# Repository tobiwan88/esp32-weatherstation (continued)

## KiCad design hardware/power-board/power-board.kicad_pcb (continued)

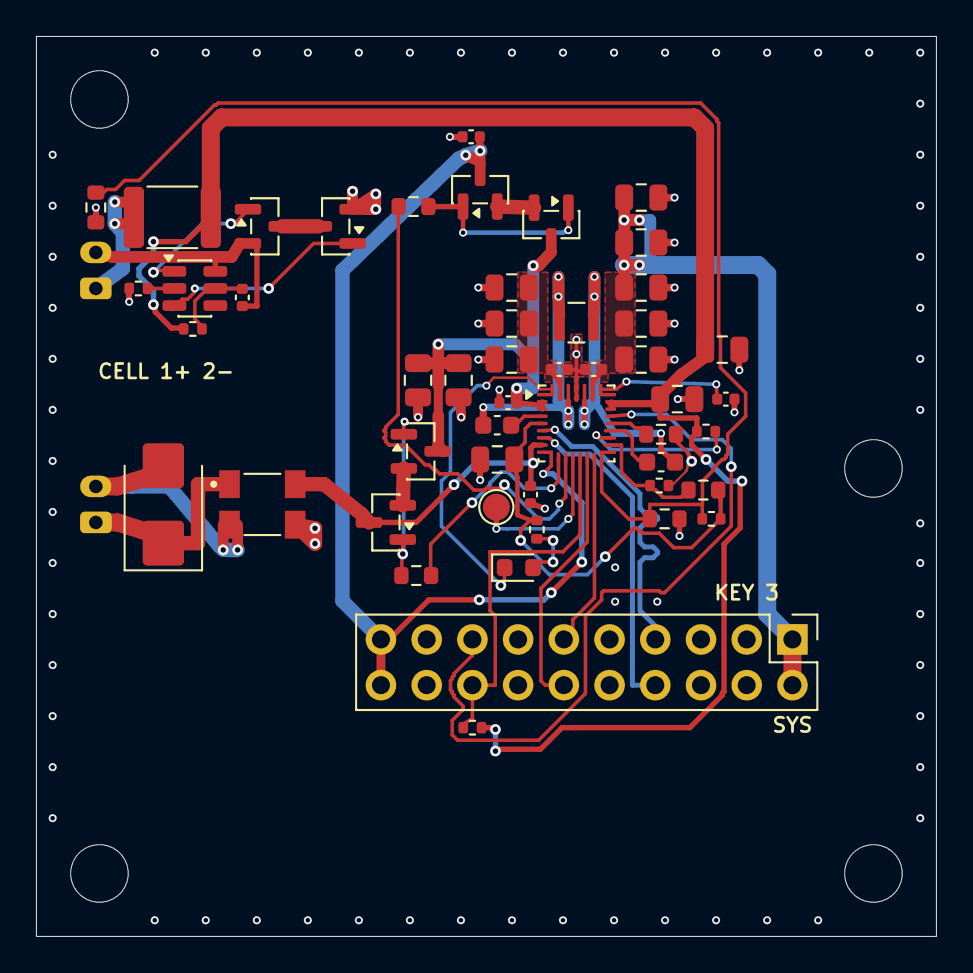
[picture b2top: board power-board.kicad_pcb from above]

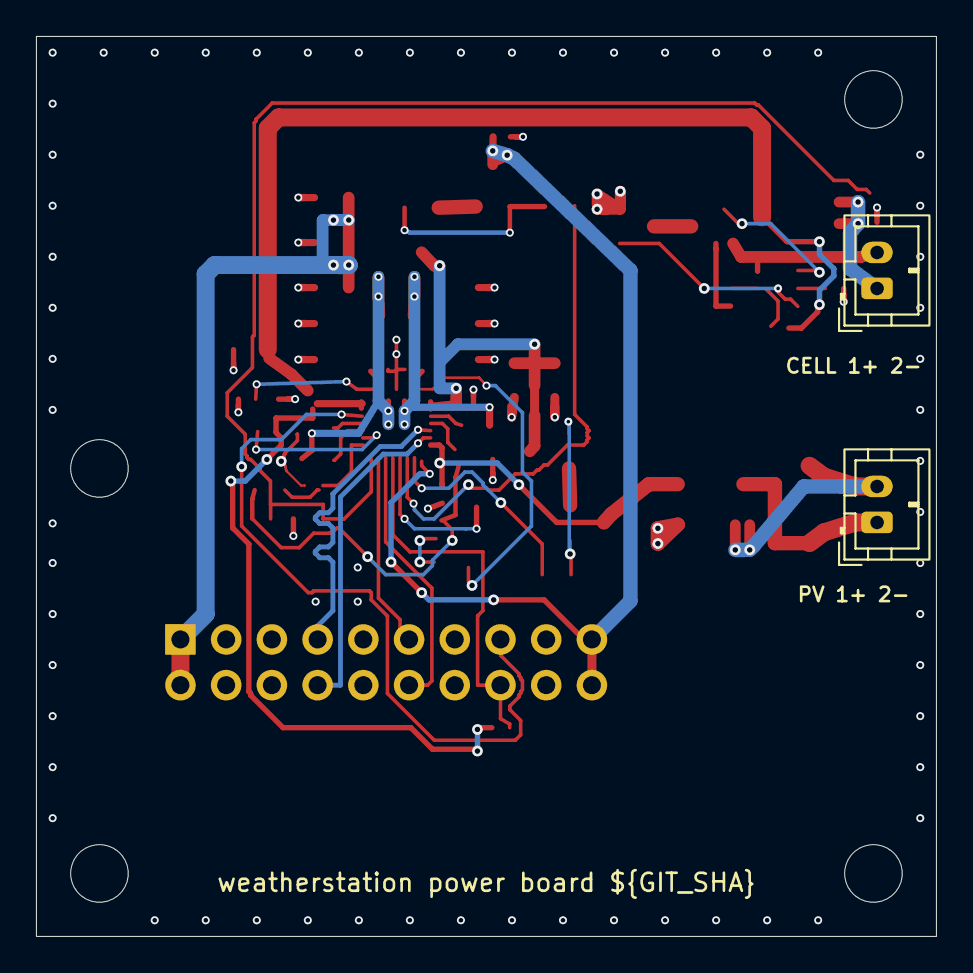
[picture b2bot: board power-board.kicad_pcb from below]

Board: 4 copper layers, 50.0 x 50.0 mm, 56 parts (2 on the bottom side), 41 nets.

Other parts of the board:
H1, H2, H3, H4: MountingHole_3.2mm_M3_ISO7380

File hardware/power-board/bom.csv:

Comment,Designator,Footprint,Quantity,LCSC Part #,Class,Status,Function / notes
AO3400A,"M1,M2,M3,M4,M60,M61",Package_TO_SOT_SMD:SOT-23,6,C20917,Basic,VERIFIED LCSC part (class: boardgen.JLC_CLASS; stock: hw-check.sh --stock; datasheet values open),"M1: AO3400A ACFET1 (N-channel, BQ25798 back-to-back); M2: AO3400A RBFET1 (N-channel, BQ25798 back-to-back); M3: AO3400A ACFET2 (N-channel, BQ25798 back-to-back); M4: AO3400A RBFET2 (N-channel, BQ25798 back-to-back); M60: AO3400A discharge FET (OD); M61: AO3400A charge FET (OC)"
300,"R11,R12",Resistor_SMD:R_0603_1608Metric,2,C23025,Basic,VERIFIED LCSC part (class: boardgen.JLC_CLASS; stock: hw-check.sh --stock; datasheet values open),R11: 300 (candidate; figure 294); R12: 300 (candidate; figure 294)
0.1u,"C1,C2,C6,C9,C13,C60",Capacitor_SMD:C_0402_1005Metric,6,C307331,Basic,VERIFIED LCSC part (class: boardgen.JLC_CLASS; stock: hw-check.sh --stock; datasheet values open),C60: 0.1u (HY2112 VDD)
SMBJ10A,D1,Diode_SMD:D_SMB,1,C151250,Extended,VERIFIED LCSC part (class: boardgen.JLC_CLASS; stock: hw-check.sh --stock; datasheet values open),"D1: SMBJ10A (PV surge, standoff 10 V, clamp 17 V)"
CMC 90R 3A,L3,weatherstation:CMF4532F_4P,1,C963746,Extended,VERIFIED LCSC part (class: boardgen.JLC_CLASS; stock: hw-check.sh --stock; datasheet values open),L3: CM choke 90 ohm 3 A (CMF4532F-900-2P-T; datasheet page to confirm)
PV IN 1+ 2-,J5,Connector_JST:JST_PH_B2B-PH-K_1x02_P2.00mm_Vertical,1,n/a,n/a,HAND-SOLDER,"J5: PV IN (1 +, 2 -)"
BQ25798RQMR,U3,Package_DFN_QFN:Texas_RQM0029A_VQFN-29_4x4mm_P0.4mm,1,C2876593,Extended,VERIFIED LCSC part (class: boardgen.JLC_CLASS; stock: hw-check.sh --stock; datasheet values open),
1uH,L1,weatherstation:L_TDK_VLS252010,1,C88211,Extended,VERIFIED LCSC part (class: boardgen.JLC_CLASS; stock: hw-check.sh --stock; datasheet values open),"L1: 1uH (TDK VLS252010HBX-1R0M-1: Isat 3.22 A, Itemp 2.55 A, 65 mohm max)"
47n,"C3,C4",Capacitor_SMD:C_0603_1608Metric,2,C1622,Basic,VERIFIED LCSC part (class: boardgen.JLC_CLASS; stock: hw-check.sh --stock; datasheet values open),
4.7u 25V,C5,Capacitor_SMD:C_0805_2012Metric,1,C1779,Basic,VERIFIED LCSC part (class: boardgen.JLC_CLASS; stock: hw-check.sh --stock; datasheet values open),
10u,"C7,C8,C10,C11,C12,C14,C15,C16,C17,C18,C19,C20",Capacitor_SMD:C_0805_2012Metric,12,C15850,Basic,VERIFIED LCSC part (class: boardgen.JLC_CLASS; stock: hw-check.sh --stock; datasheet values open),
1n,C21,Capacitor_SMD:C_0402_1005Metric,1,C1523,Basic,VERIFIED LCSC part (class: boardgen.JLC_CLASS; stock: hw-check.sh --stock; datasheet values open),
100,"R13,R60",Resistor_SMD:R_0402_1005Metric,2,C25076,Basic,VERIFIED LCSC part (class: boardgen.JLC_CLASS; stock: hw-check.sh --stock; datasheet values open),R60: 100 (HY2112 VDD)
3.0k,R14,Resistor_SMD:R_0603_1608Metric,1,C4211,Basic,VERIFIED LCSC part (class: boardgen.JLC_CLASS; stock: hw-check.sh --stock; datasheet values open),"R14: 3.0k (PROG: 1S, 1.5 MHz)"
120k,R15,Resistor_SMD:R_0603_1608Metric,1,C25808,Basic,VERIFIED LCSC part (class: boardgen.JLC_CLASS; stock: hw-check.sh --stock; datasheet values open),R15: 120k (ILIM: REGN 5 V x 100/220 = 2.27 V -> 1.59 A clamp)
100k,R16,Resistor_SMD:R_0402_1005Metric,1,C25741,Basic,VERIFIED LCSC part (class: boardgen.JLC_CLASS; stock: hw-check.sh --stock; datasheet values open),
5.1k,R17,Resistor_SMD:R_0402_1005Metric,1,C25905,Basic,VERIFIED LCSC part (class: boardgen.JLC_CLASS; stock: hw-check.sh --stock; datasheet values open),R17: 5.1k (TS top; thresholds about +0.9 C vs 5.24k/30.31k)
30k,R18,Resistor_SMD:R_0603_1608Metric,1,C22984,Basic,VERIFIED LCSC part (class: boardgen.JLC_CLASS; stock: hw-check.sh --stock; datasheet values open),R18: 30k (TS bottom)
2.2k,R19,Resistor_SMD:R_0402_1005Metric,1,C25879,Basic,VERIFIED LCSC part (class: boardgen.JLC_CLASS; stock: hw-check.sh --stock; datasheet values open),
STAT red,D2,LED_SMD:LED_0603_1608Metric,1,C2286,Basic,VERIFIED LCSC part (class: boardgen.JLC_CLASS; stock: hw-check.sh --stock; datasheet values open),
330k,R23,Resistor_SMD:R_0402_1005Metric,1,C25778,Extended,VERIFIED LCSC part (class: boardgen.JLC_CLASS; stock: hw-check.sh --stock; datasheet values open),R23: 330k (CE pull-up to BAT_PACK)
PTC 3A,F1,Fuse:Fuse_1812_4532Metric,1,C21004,Extended,VERIFIED LCSC part (class: boardgen.JLC_CLASS; stock: hw-check.sh --stock; datasheet values open),F1: PTC 3 A hold (SMD1812P300TF)
CELL 1+ 2-,J6,Connector_JST:JST_PH_B2B-PH-K_1x02_P2.00mm_Vertical,1,n/a,n/a,HAND-SOLDER,"J6: CELL (1 +, 2 -)"
10k NTC,TH1,Resistor_SMD:R_0603_1608Metric,1,C13564,Extended,VERIFIED LCSC part (class: boardgen.JLC_CLASS; stock: hw-check.sh --stock; datasheet values open),"TH1: 10k NTC NCP18XH103F03RB (TS, next to J6)"
HY2112-CB,U6,Package_TO_SOT_SMD:SOT-23-6,1,C168764,Extended,VERIFIED LCSC part (class: boardgen.JLC_CLASS; stock: hw-check.sh --stock; datasheet values open),U6: HY2112-CB LiFePO4 protection
2k,R61,Resistor_SMD:R_0402_1005Metric,1,C4109,Basic,VERIFIED LCSC part (class: boardgen.JLC_CLASS; stock: hw-check.sh --stock; datasheet values open),R61: 2k (HY2112 CS)
J_PWR 2x10 key 3,J10,Connector_PinHeader_2.54mm:PinHeader_2x10_P2.54mm_Vertical,1,n/a,n/a,HAND-SOLDER,"J10: J_PWR 2x10 keyed 2.54 mm (power side: socket, hole 3 blocked; hand-solder)"
Test points,TP3,TestPoint:TestPoint_Pad_D1.5mm,1,n/a,n/a,PCB pads only,test pads

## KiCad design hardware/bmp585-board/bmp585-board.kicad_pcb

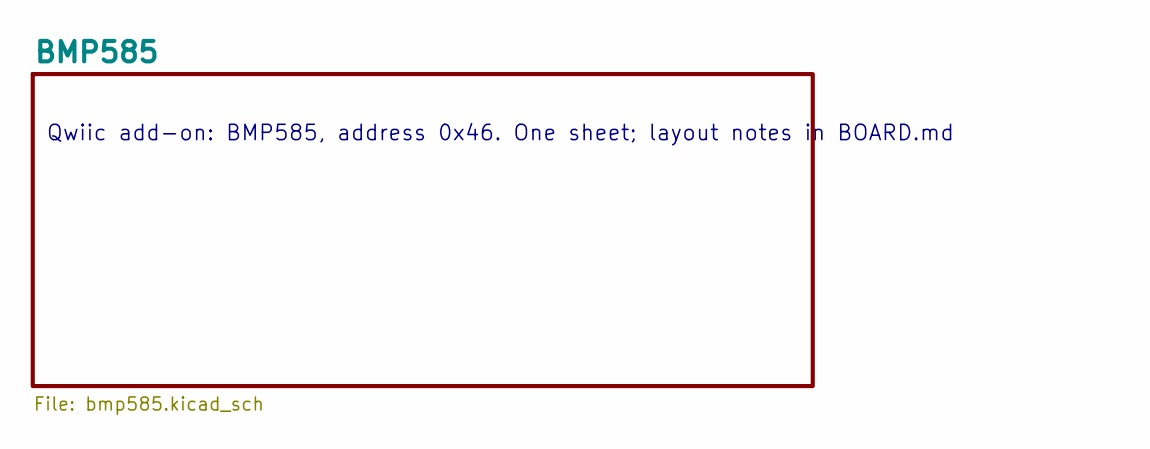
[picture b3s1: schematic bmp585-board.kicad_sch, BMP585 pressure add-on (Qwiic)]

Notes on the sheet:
Qwiic add-on: BMP585, address 0x46. One sheet; layout notes in BOARD.md

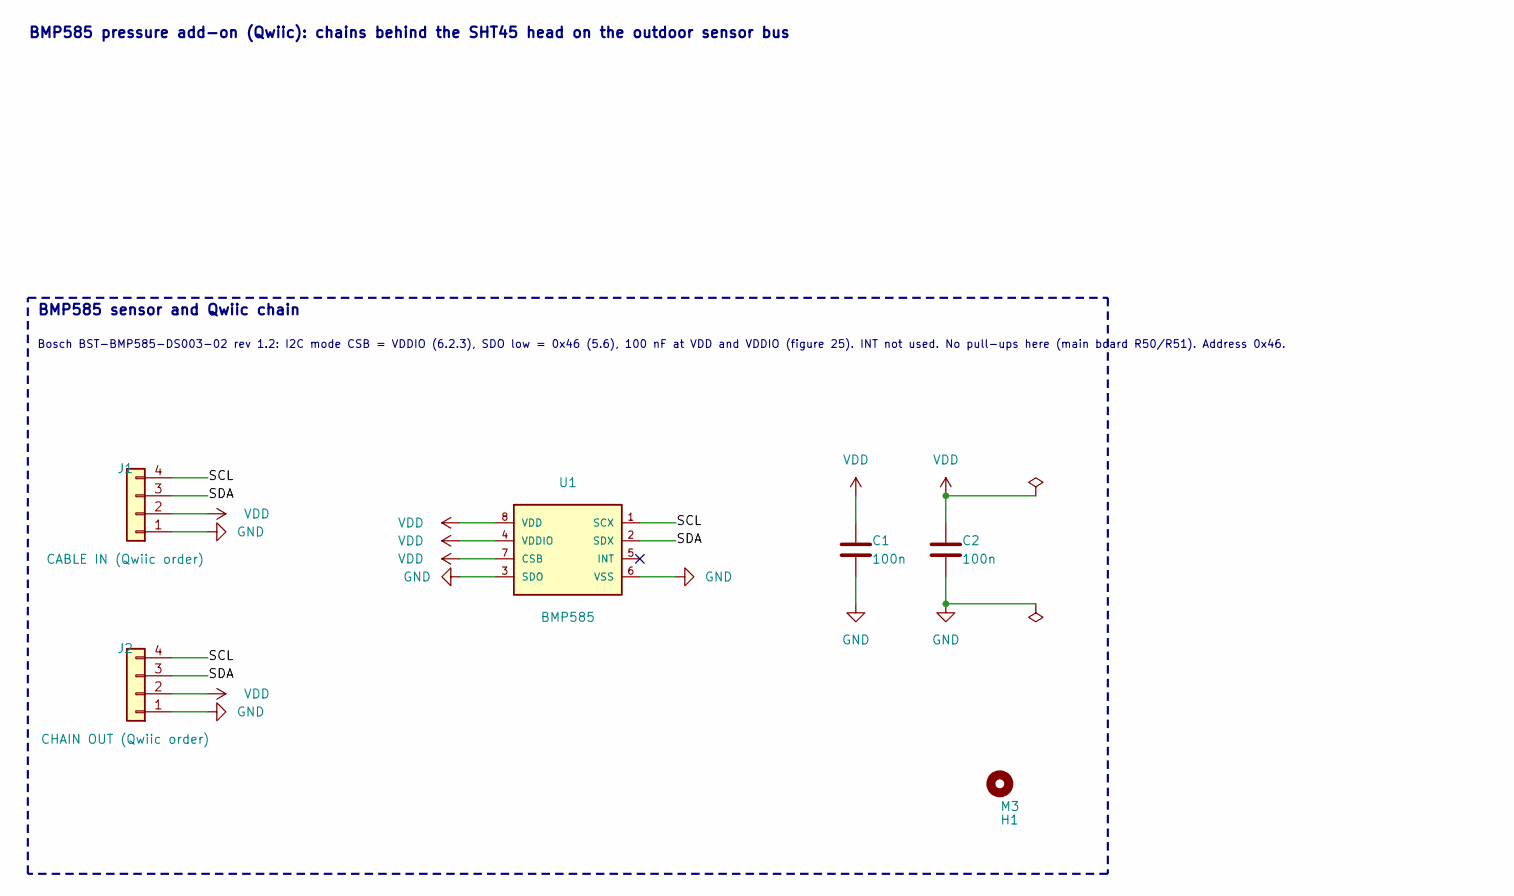
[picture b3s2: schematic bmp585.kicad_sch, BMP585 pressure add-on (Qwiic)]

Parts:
C1, C2: 100n; C_0603_1608Metric; LCSC C14663
H1: M3; MountingHole_3.2mm_M3
J1: CABLE IN (Qwiic order); JST_SH_SM04B-SRSS-TB_1x04-1MP_P1.00mm_Horizontal; LCSC C160404
J2: CHAIN OUT (Qwiic order); JST_SH_SM04B-SRSS-TB_1x04-1MP_P1.00mm_Horizontal; LCSC C160404
U1: BMP585; BMP585_LGA-8_3.25x3.25mm; LCSC C18184976

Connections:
/BMP585/SCL: J1.4, J2.4, U1.1 (SCX)
/BMP585/SDA: J1.3, J2.3, U1.2 (SDX)
GND: C1.2, C2.2, J1.1, J2.1, U1.3 (SDO), U1.6 (VSS)
VDD: C1.1, C2.1, J1.2, J2.2, U1.4 (VDDIO), U1.7 (CSB), U1.8 (VDD)

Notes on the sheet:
BMP585 sensor and Qwiic chain
Bosch BST-BMP585-DS003-02 rev 1.2: I2C mode CSB = VDDIO (6.2.3), SDO low = 0x46 (5.6), 100 nF at VDD and VDDIO (figure 25). INT not used. No pull-ups here (main board R50/R51). Address 0x46.
BMP585 pressure add-on (Qwiic): chains behind the SHT45 head on the outdoor sensor bus

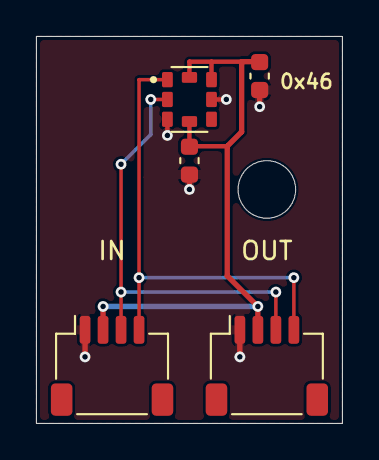
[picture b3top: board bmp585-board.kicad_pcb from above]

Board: 2 copper layers, 17.0 x 21.5 mm, 6 parts (0 on the bottom side), 4 nets.

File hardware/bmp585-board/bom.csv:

Comment,Designator,Footprint,Quantity,LCSC Part #,Class
BMP585,U1,weatherstation:BMP585_LGA-8_3.25x3.25mm,1,C18184976,Extended
100n,C1,Capacitor_SMD:C_0603_1608Metric,1,C14663,Basic
100n,C2,Capacitor_SMD:C_0603_1608Metric,1,C14663,Basic
CABLE IN (Qwiic order),J1,Connector_JST:JST_SH_SM04B-SRSS-TB_1x04-1MP_P1.00mm_Horizontal,1,C160404,Extended
CHAIN OUT (Qwiic order),J2,Connector_JST:JST_SH_SM04B-SRSS-TB_1x04-1MP_P1.00mm_Horizontal,1,C160404,Extended

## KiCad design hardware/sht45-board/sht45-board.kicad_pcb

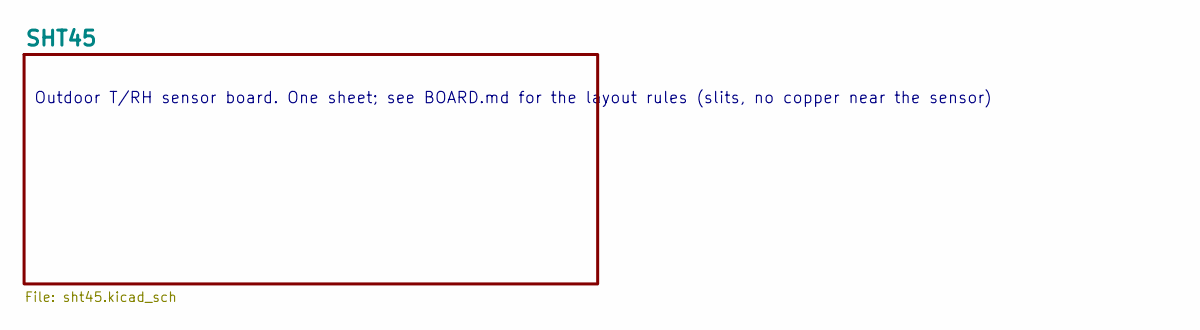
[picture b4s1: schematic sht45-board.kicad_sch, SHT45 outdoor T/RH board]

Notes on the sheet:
Outdoor T/RH sensor board. One sheet; see BOARD.md for the layout rules (slits, no copper near the sensor)

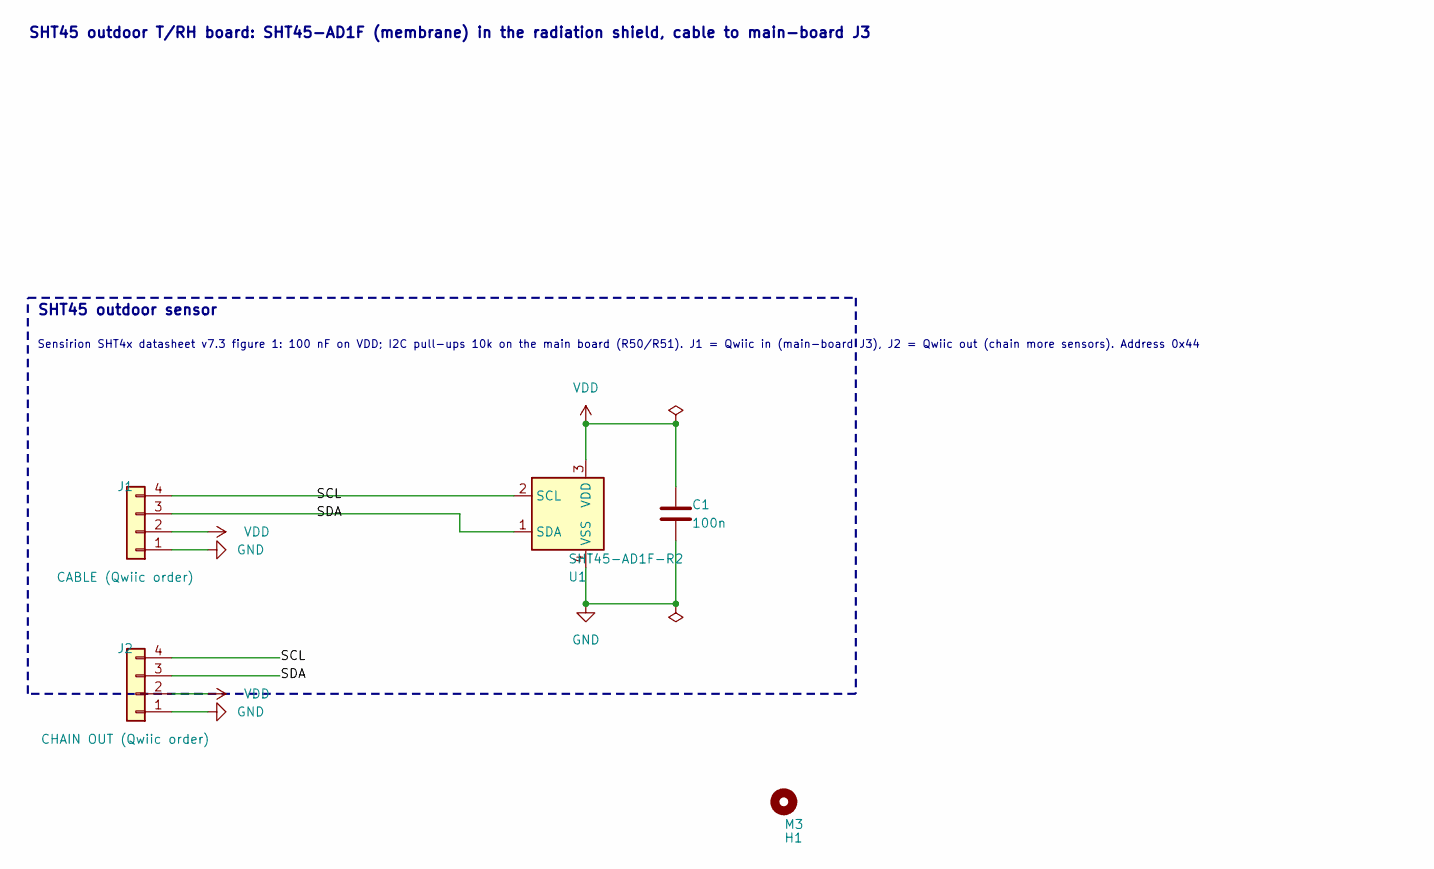
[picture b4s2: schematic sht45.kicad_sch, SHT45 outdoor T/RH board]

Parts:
C1: 100n; C_0603_1608Metric; LCSC C14663
H1: M3; MountingHole_3.2mm_M3
J1: CABLE (Qwiic order); JST_SH_SM04B-SRSS-TB_1x04-1MP_P1.00mm_Horizontal; LCSC C160404
J2: CHAIN OUT (Qwiic order); JST_SH_SM04B-SRSS-TB_1x04-1MP_P1.00mm_Horizontal; LCSC C160404
U1: SHT45-AD1F-R2; Sensirion_DFN-4_1.5x1.5mm_P0.8mm_SHT4x_NoCentralPad; LCSC C5360602

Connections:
/SHT45/SCL: J1.4, J2.4, U1.2 (SCL)
/SHT45/SDA: J1.3, J2.3, U1.1 (SDA)
GND: C1.2, J1.1, J2.1, U1.4 (VSS)
VDD: C1.1, J1.2, J2.2, U1.3 (VDD)

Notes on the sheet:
SHT45 outdoor sensor
Sensirion SHT4x datasheet v7.3 figure 1: 100 nF on VDD; I2C pull-ups 10k on the main board (R50/R51). J1 = Qwiic in (main-board J3), J2 = Qwiic out (chain more sensors). Address 0x44
SHT45 outdoor T/RH board: SHT45-AD1F (membrane) in the radiation shield, cable to main-board J3

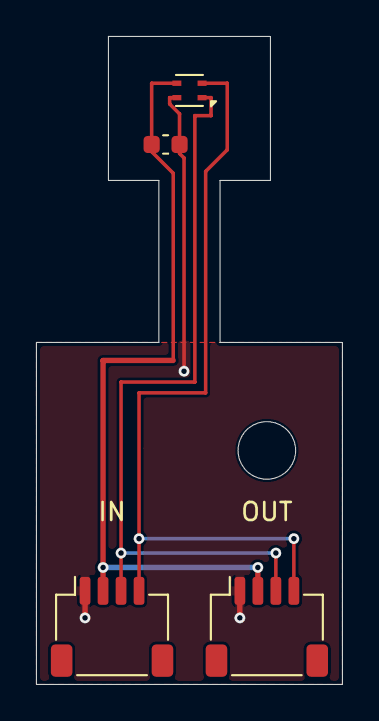
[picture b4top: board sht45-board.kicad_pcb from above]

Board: 2 copper layers, 17.0 x 36.0 mm, 5 parts (0 on the bottom side), 4 nets.

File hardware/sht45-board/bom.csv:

Comment,Designator,Footprint,Quantity,LCSC Part #,Class
SHT45-AD1F-R2,U1,Sensor_Humidity:Sensirion_DFN-4_1.5x1.5mm_P0.8mm_SHT4x_NoCentralPad,1,C5360602,Extended
100n,C1,Capacitor_SMD:C_0603_1608Metric,1,C14663,Basic
CABLE (Qwiic order),J1,Connector_JST:JST_SH_SM04B-SRSS-TB_1x04-1MP_P1.00mm_Horizontal,1,C160404,Extended
CHAIN OUT (Qwiic order),J2,Connector_JST:JST_SH_SM04B-SRSS-TB_1x04-1MP_P1.00mm_Horizontal,1,C160404,Extended

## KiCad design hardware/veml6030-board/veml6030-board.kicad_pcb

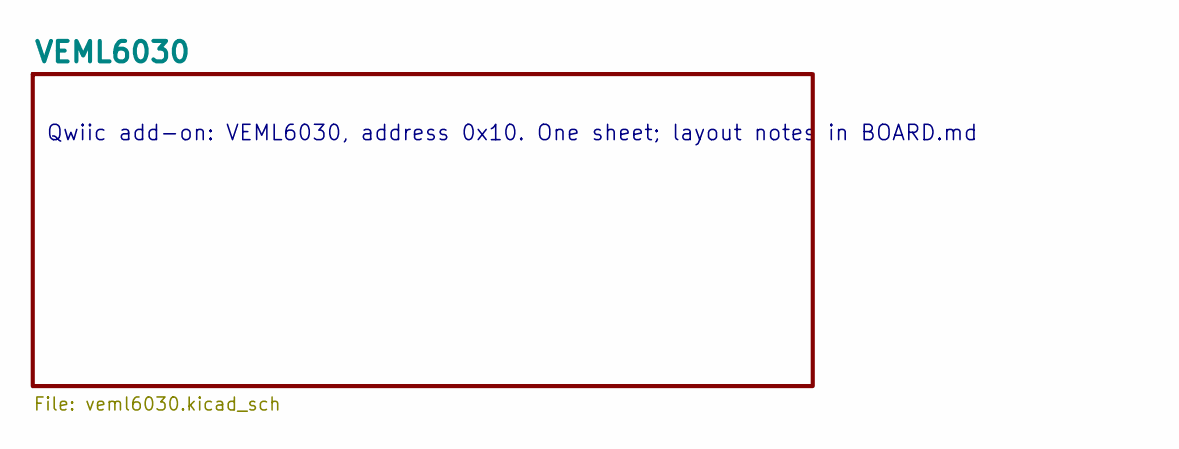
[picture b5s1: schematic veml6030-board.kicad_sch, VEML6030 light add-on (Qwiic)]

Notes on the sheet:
Qwiic add-on: VEML6030, address 0x10. One sheet; layout notes in BOARD.md

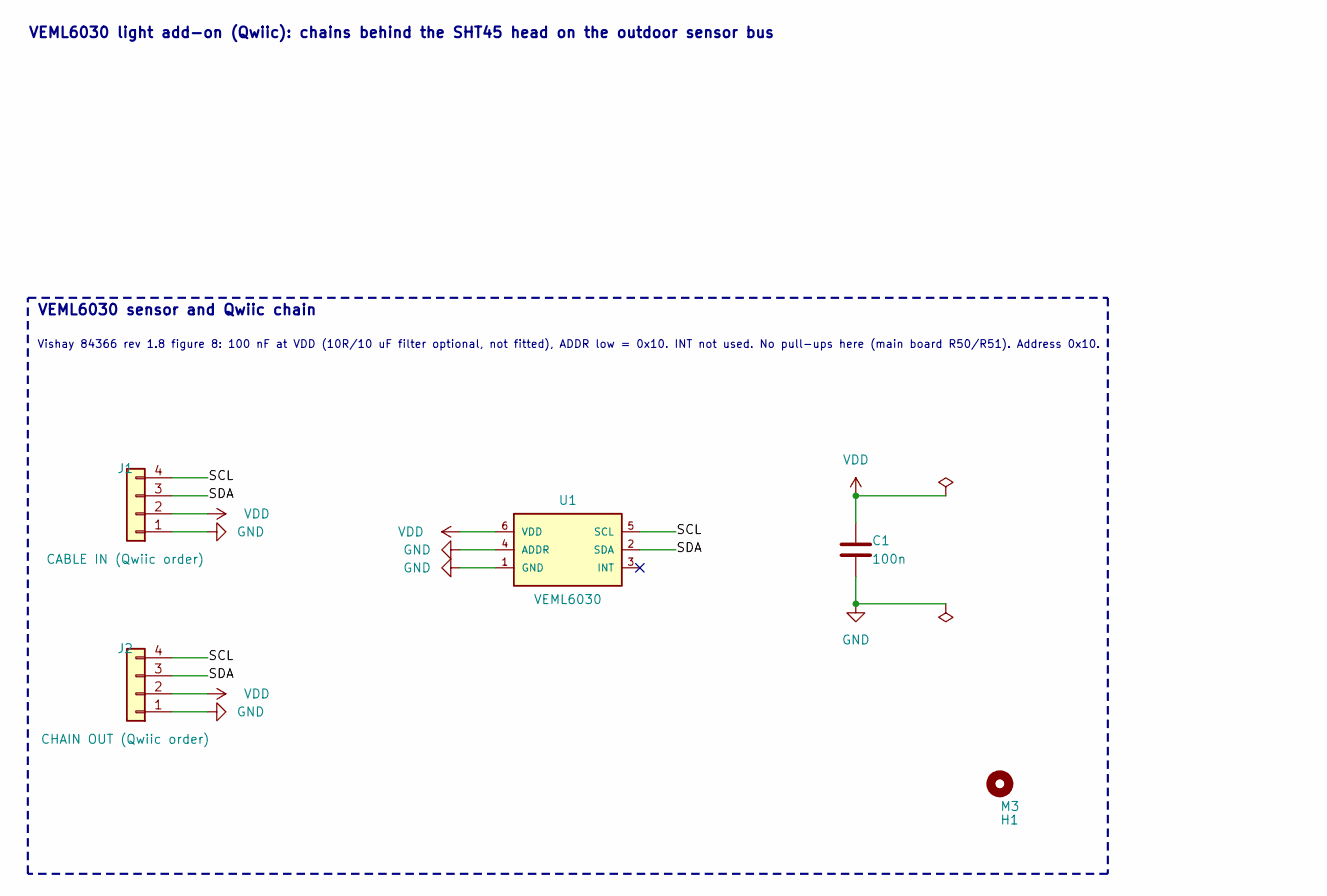
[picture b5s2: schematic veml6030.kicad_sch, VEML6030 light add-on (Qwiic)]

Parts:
C1: 100n; C_0603_1608Metric; LCSC C14663
H1: M3; MountingHole_3.2mm_M3
J1: CABLE IN (Qwiic order); JST_SH_SM04B-SRSS-TB_1x04-1MP_P1.00mm_Horizontal; LCSC C160404
J2: CHAIN OUT (Qwiic order); JST_SH_SM04B-SRSS-TB_1x04-1MP_P1.00mm_Horizontal; LCSC C160404
U1: VEML6030; Vishay_VEML6030_2x2mm; LCSC C132182

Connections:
/VEML6030/SCL: J1.4, J2.4, U1.5 (SCL)
/VEML6030/SDA: J1.3, J2.3, U1.2 (SDA)
GND: C1.2, J1.1, J2.1, U1.1 (GND), U1.4 (ADDR)
VDD: C1.1, J1.2, J2.2, U1.6 (VDD)

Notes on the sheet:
VEML6030 sensor and Qwiic chain
Vishay 84366 rev 1.8 figure 8: 100 nF at VDD (10R/10 uF filter optional, not fitted), ADDR low = 0x10. INT not used. No pull-ups here (main board R50/R51). Address 0x10.
VEML6030 light add-on (Qwiic): chains behind the SHT45 head on the outdoor sensor bus

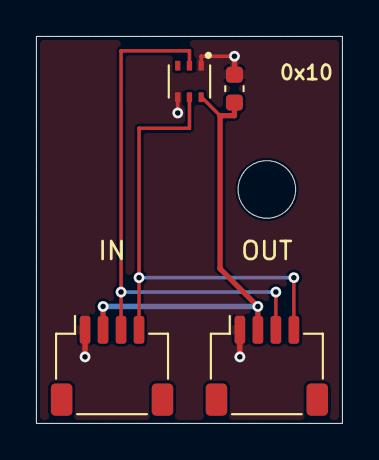
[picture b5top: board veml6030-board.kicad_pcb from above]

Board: 2 copper layers, 17.0 x 21.5 mm, 5 parts (0 on the bottom side), 4 nets.

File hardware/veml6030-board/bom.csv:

Comment,Designator,Footprint,Quantity,LCSC Part #,Class
VEML6030,U1,weatherstation:Vishay_VEML6030_2x2mm,1,C132182,Extended
100n,C1,Capacitor_SMD:C_0603_1608Metric,1,C14663,Basic
CABLE IN (Qwiic order),J1,Connector_JST:JST_SH_SM04B-SRSS-TB_1x04-1MP_P1.00mm_Horizontal,1,C160404,Extended
CHAIN OUT (Qwiic order),J2,Connector_JST:JST_SH_SM04B-SRSS-TB_1x04-1MP_P1.00mm_Horizontal,1,C160404,Extended

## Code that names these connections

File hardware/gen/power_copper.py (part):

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What is drawn (sources in BOARD.md "Routing"):
  1. BQ25798 power stage as weatherstation-v1 (SLUSDV2C 8.4.1 items 1-7, figure 8-21): PMID/SYS 0402 caps on the
     pin row with F.Cu pours, SW1/SW2 through vias under the IC to L1 beyond the caps, GND pin pour with two plane
     vias, bulk caps joined by pours, BTST/REGN/PROG/ILIM/BATP/SDRV/INT fan-out on the right and left pin columns.
  2. Input paths: VBUS node (M4, C7/C8, C6, M2) with the v1 B.Cu lane, ACFET1/RBFET1 pair M1/M2, PV entry
     J5 -> D1 -> L3 -> M3 -> M4, USB_VBUS trunk J10.19/20 -> M1 on B.Cu.
  3. Battery path: J6 -> F1 -> BAT_PACK trunk (F.Cu, north edge) -> C20/C19 -> BAT pins; BAT_N to U6/M60, PB_MID,
     M61 source to the GND planes; SYS from the SYS bulk caps on B.Cu to J10.1/2.
  4. BC1.2 stub pair J10.7/8 -> U3.6/7 on B.Cu (one via each under U3, length matched), GND stitching beside it.
  5. U3 bottom row south band (CE, SCL, SDA to J10, escape vias for VAC1/ACDRV1/ACDRV2/QON) and TS.
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    assert c.rot("L1") == 0 and c.pad("L1", "1")[0] < c.pad("L1", "2")[0], "L1 SW1 pad left"
    r = lambda pts: [(ux + x, uy + y) for x, y in pts]  # noqa: E731

    # pours: PMID (left) and SYS (right) over the 0402 cap and bulk cap pads; GND pin pour between C9/C13 to 2 vias
    pmid = [(-1.0, -1.3), (-0.8, -1.3), (-0.8, -2.45), (-1.1, -2.45), (-1.1, -3.5), (-1.6, -3.5), (-1.6, -8.4),
            (-3.25, -8.4), (-3.25, -2.8), (-1.75, -2.8), (-1.75, -2.3), (-1.0, -2.3)]
    c.z("PMID", "F", r(pmid))
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    # SYS bulk caps above the pour joined to it at class width
    c.t("SYS", "F", CH, r([(2.655, -7.55), (2.655, -12.55)]))

    # left column: VBUS pins to C6 and a 0.6/0.3 via beside it (v1 VBUS lane on B.Cu), BTST1 to C3, REGN to C5,
    # USB D+/D- into the body to their vias (pair, see bc12()), PV_IN (VAC2) left and down to C2
    c6 = c.pad("C6", "1")
    c.t("VBUS", "F", 0.3, [c.pad("U3", "2"), (ux - 1.9, uy - 1.0), c.pad("U3", "3")])
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    c.t("/Charger/PV_IN", "F", 0.3, [c.pad("U3", "8"), (c2[0] + 0.17, uy + 1.2), (c2[0] + 0.02, uy + 1.35),
                                     (c2[0] + 0.02, c2[1] - 0.1), c2])

    # STAT (top-left corner pin) out through the corner notch, west in the channel under the PMID pour, to a via in
    # the pocket between C7, C10 and C6 (the router continues on B.Cu to the debug LED D2)
    stat_v = (ux - 5.0, uy - 2.1)
    c.t("/Charger/STAT", "F", 0.15, [(ux - 1.38, uy - 1.9), (ux - 2.0, uy - 1.9), (ux - 2.64, uy - 2.54),
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    c.t("REGN", "F", 0.25, [c.pad("R15", "1"), (c.pad("R17", "1")[0], c.pad("R15", "1")[1] + 0.5),
                            c.pad("R17", "1")])

    # right column in pin order (no crossings): SDRV via to C21, BAT pins to C19, INT to its via, PROG to R14,
    # BTST2 to C4, BATP under the body and B.Cu to R13 (sense trace away from SW2, item 6), ILIM to R16, TS to R18
    c.t("/Charger/SDRV", "F", 0.2, [(ux + 1.35, uy - 1.9), (ux + 2.2, uy - 1.9), (ux + 2.775, uy - 2.325)])
    c.v("/Charger/SDRV", ux + 2.775, uy - 2.325)
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
def south_band(c, ux, uy):
    """U3 bottom row to J10 (CE, SCL, SDA all on F.Cu, nested so nothing crosses; BOARD.md "Routing"), and escape
    stubs with staggered vias for the west-bound pins (VAC1, ACDRV2, ACDRV1, QON), 0.45 mm vias 1 mm apart."""
    assert c.rot("J10") == 270, "J10 pin 1 at the right end"
    p = lambda n: c.pad("U3", str(n))  # noqa: E731
    j = lambda n: c.pad("J10", str(n))  # noqa: E731
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

def battery(c, ux, uy):
    """Cell path: J6.1 -> F1 -> BAT_PACK trunk along the north edge -> C20 -> C19/BAT pins; J6.2 BAT_N -> U6 VSS,
    C60 -> M60 -> PB_MID -> M61 -> GND planes; SYS bulk caps -> B.Cu -> J10.1/2. Widths: Charge class or wider."""
    assert c.rot("F1") == 0 and c.rot("M60") == 0 and c.rot("M61") == 180 and c.rot("J6") == 90
    j61, j62 = c.pad("J6", "1"), c.pad("J6", "2")
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
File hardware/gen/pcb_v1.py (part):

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    "H1": (3.5, 3.5, 0), "H2": (W - 3.5, 3.5, 0), "H3": (3.5, H - 3.5, 0), "H4": (W - 3.5, H - 3.5, 0),
    # battery: cell connector on the left edge, NTC beside it
    "J6": (3.3, 14.0, 270, "B"), "U6": (8.8, 14.0, 0),
    # pinned 2026-11-03 at their NEAR positions (the BAT_PACK trunk lands next to F1.2 and M60)
    "F1": (7.55, 10.25, 0), "M60": (12.688, 10.55, 0), "C60": (11.438, 14.5, -90), "R60": (8.688, 16.25, 0),
    # debug corner
    "J7": (48.0, 16.5, 0, "B"), "JP1": (40.5, 10.3, 0), "JP2": (40.5, 12.8, 0),  # tweezer pads
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         if not r.startswith("H") and r != "U1" else p for r, p in FIXED.items()}

# BQ25798 power stage drawn by hand (SLUSDV2C 8.4.1/8.4.2, priority order): 0402 PMID and SYS caps on top of the
# PMID-SW1-GND-SW2-SYS pin row sharing the GND pin; SW1/SW2 drop through vias under the IC to B.Cu and come back up at
# the inductor above the caps; bulk caps in a column beside each, joined by F.Cu pours. Offsets from U3's centre (mm).
CHARGER = {
    "C9": (-0.95, -3.0, 0), "C13": (0.95, -3.0, 180), "L1": (0.0, -5.6, 0),
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    "C14": (3.6, -3.55, 0), "C15": (3.6, -5.55, 0), "C16": (3.6, -7.55, 0), "C17": (3.6, -10.05, 0), "C20": (8.1, -4.1, 0),
    "C18": (3.6, -12.55, 0),
    # small parts, one ring around the pins in pin order so every pin fans out without crossing (items 3-5, 7):
    # right: BAT cap beside the BAT pins, then PROG, BTST2, ILIM, TS rows; BATP sense and SDRV cap further out
    "C19": (5.6, -1.35, 0), "C21": (8.3, -1.35, 0), "R14": (4.7, 0.6, 0), "R13": (7.2, 0.45, 0),
    "C4": (4.7, 2.15, 0), "R16": (4.6, 3.45, 0), "R15": (7.05, 3.7, 180), "R18": (4.9, 5.3, 0), "R17": (7.5, 5.3, 180),
    # left: VBUS 100 nF at the VBUS pins, BTST1 cap, REGN cap (2 GND vias to the plane, item 3)
    "C6": (-3.45, -1.15, 180), "C3": (-4.4, 0.1, 180), "C5": (-4.4, 1.75, 180),
    # ACFET1/RBFET1 output FET M2: its VBUS pin at the top of the hand-drawn VBUS channel
    "M2": (-1.4, -11.05, -90),
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             (_DP, 15.3, 35.85), (_DN, 15.3, 36.6), (_DN, 9.25, 28.745), ("GND", 8.9, 33.4)],
}
# Charge trunks at class width, absolute board mm (the autorouter necks these down to 0.2 mm in the crowded middle):
# BAT_PACK from the bulk cap C20 on B.Cu diagonally under U1's pin column to two 0.6/0.3 vias, up to the fuse F1;
# USB_VBUS from J1's A4/B9 pad right of the shell keepout, between M1 and U4, to M1's source.
TRUNKS = {"pours": [], "tracks": [
    ("BAT_PACK", "F", 0.5, [(23.275, 30.125), (24.075, 30.125)]), ("BAT_PACK", "F", 0.65, [(23.655, 30.125), (23.655, 30.9)]),
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    return [(-x, y) for x, y in pts]


# bottom edge raised to -2.8 left of x -1.75 (still covers the C10/C14 pads): a channel above the pin row for STAT
# (left) and SDRV (right, mirrored SYS pour)
_PMID = [(-1.0, -1.3), (-0.8, -1.3), (-0.8, -2.45), (-1.1, -2.45), (-1.1, -3.5), (-1.6, -3.5), (-1.6, -8.4),
         (-3.25, -8.4), (-3.25, -2.8), (-1.75, -2.8), (-1.75, -2.3), (-1.0, -2.3)]
_SW1_B = [(-0.45, 0.25), (-0.45, -0.55), (-1.0, -1.1), (-1.0, -7.85)]
# U3 bottom row (net, pin x, bend y, via x): ACDRV2, ACDRV1, CE, SCL, SDA, TS (pin 12 QON unused)
_FAN = [("/Charger/ACDRV2", -1.0, 2.7, -1.1), ("/Charger/ACDRV1", -0.6, 2.6, -0.3), ("/Charger/CHG_CE", 0.2, 2.6, 0.5),
        ("/Charger/CHG_SCL", 0.6, 2.5, 1.3), ("/Charger/CHG_SDA", 1.0, 2.4, 2.1), ("/Battery/TS", 1.85, 2.6, 2.9)]
# off by default: trial 7 (2026-11-03) closed the bottom-row nets but the via row cut the channel under U3 (10 open
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        ("VBUS", "F", 0.4, [(-3.0, -1.95), (-2.97, -1.3)]), ("VBUS", "F", 0.3, [(-2.97, -1.15), (-1.9, -1.0)]),
        ("VBUS", "B", 0.65, [(-3.0, -1.95), (-2.4, -2.6)]), ("VBUS", "B", 0.65, [(-2.4, -2.6), (-2.4, -8.75)]),
        ("VBUS", "F", 0.5, [(-2.4, -8.75), (-2.1, -8.75), (-1.4, -9.45)]),  # one 0.6/0.3 via (KRT drops parallel-via links)
        # STAT (top-left corner pin) left above C6 in the pour channel, down beside C3/C5 to the debug LED D2
        # (pins 1 and 24 are L-shaped corner pads open toward the corner: the stubs leave through that notch)
        ("/Charger/STAT", "F", 0.2, [(-1.38, -1.9), (-2.0, -1.9), (-2.65, -2.55), (-4.75, -2.55), (-6.05, -1.25),
                                     (-6.05, 3.1), (-6.29, 3.5)]),
        # SDRV (top-right corner pin) right in the SYS pour channel, above C19, down to its 1 nF C21
        # left pins in one fan: BTST1 and REGN to their caps, VAC2 (PV_IN sense, uA) between pins 7 and 9 at the
        # 0.3 mm charge-class floor (0.15 mm each side), down past the REGN cap to C2
        ("/Charger/BTST1", "F", 0.2, [(-1.9, -0.4), (-2.9, -0.4), (-3.3, 0.0)]),
        ("REGN", "F", 0.2, [(-1.9, 0.0), (-2.55, 0.0), (-2.85, 0.3), (-2.85, 1.05), (-3.3, 1.5)]),
        ("/Charger/PV_IN", "F", 0.3, [(-1.9, 1.2), (-2.3, 1.2), (-2.65, 1.55), (-2.65, 3.1), (0.11, 5.86), (0.11, 6.45)]),
        # right column in pin order (no crossings): PROG into R14's upper pad half, BTST2 down to C4, BATP through a
        # via under the body (clear of the SW2 vias) and B.Cu to R13, ILIM down to R16, TS from the corner pad's
        # inner arm down to R18, INT to a via for its long run to the MCU; BAT pins to the BAT cap at 0.4 mm
        ("/Charger/PROG", "F", 0.2, [(1.9, 0.0), (3.0, 0.0), (3.25, 0.25), (3.5, 0.25)]),
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        ("/Battery/TS", "F", 0.2, [(1.4, 2.0), (1.4, 3.8), (2.9, 5.3), (4.0, 5.3)]),
        ("/Charger/CHG_INT", "F", 0.2, [(1.9, -0.4), (3.05, -0.5)]),
        ("BAT_PACK", "F", 0.4, [(1.9, -1.1), (4.4, -1.1)]),
        ("BAT_PACK", "F", 0.3, [(1.95, -1.2), (1.95, -0.85)]),  # BAT pins 23 and 22 joined at 0.3 mm
        # BATP sense resistor R13 to the BAT cap C19, under C19's GND pad
        ("BAT_PACK", "F", 0.3, [(6.69, 0.45), (6.69, -0.3), (4.65, -0.3), (4.65, -0.8)]),
        ("/Charger/SDRV", "F", 0.2, [(1.35, -1.9), (2.2, -1.9), (2.775, -2.325)]),
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                    taken.append((ox + min(x1, x2) - g, oy + min(y1, y2) - g, ox + max(x1, x2) + g, oy + max(y1, y2) + g))
        for net, x, y, *_ in copper["vias"]:
            taken.append((ox + x - 0.45, oy + y - 0.45, ox + x + 0.45, oy + y + 0.45))
    # escape bands for U3's signal pins (TS/ILIM/BATP/BTST2/PROG/INT on the right below BAT, the bottom row, D+/D-/
    # PV_IN on the left below REGN): no part there, so every pin can fan out before the router takes over
    for bx0, by0, bx1, by1 in ((2.4, -0.55, 4.3, 2.7), (-2.7, 2.4, 2.7, 4.3), (-4.3, 0.25, -2.4, 2.7)):
        taken.append((ux3 + bx0, uy3 + by0, ux3 + bx1, uy3 + by1))

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
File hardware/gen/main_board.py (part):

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    "R9": ("Device:R", "5.1k", R0402, "C25905", "USB"),
    "R10": ("Device:R", "5.1k", R0402, "C25905", "USB"),
    "#FLG12": ("power:PWR_FLAG", "PWR_FLAG", None, None, "USB"),
    "#FLG22": ("power:PWR_FLAG", "PWR_FLAG", None, None, "USB"),  # USB_VBUS: J1 and U4 pins are passive / power input
    # --- Header: J10 and the charger host pull-ups (moved from the old Charger sheet) ----------------------------------
    "J10": header_part("USB", "main"),
    # CE pull-up to +3V3 (not REGN: CE is also an ESP32 GPIO, 3.3 V I/O; v1 PARTS-REVIEW A7): charge off until firmware
    # has written VREG 3.65 V and drives CE low. 1M since 2026-11-21 (review B1): CE is held low through deep sleep, 3.3 uA
    # instead of 33 uA; the power board has its own pull-up to BAT_PACK (R23 330k since 2026-11-24), so CE never floats
    # on either side; with +3V3 dead and both boards mated R20/R23 hold CE at 0.75 x BAT (review B2).
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    # while the sensor rail is off (v1 PARTS-REVIEW A4).
    "R54": ("Device:R", "10k", R0402, "C25744", "USB"),
    "R55": ("Device:R", "10k", R0402, "C25744", "USB"),
    "#FLG21": ("power:PWR_FLAG", "PWR_FLAG", None, None, "USB"),  # SYS arrives through J10 (passive pins)
    # --- MCU ---------------------------------------------------------------------------------------------------------
    "U1": ("RF_Module:ESP32-S3-WROOM-1", "ESP32-S3-WROOM-1-N8", "RF_Module:ESP32-S3-WROOM-1", "C2913198", "MCU"),
    "C30": ("Device:C", "22u", C0805, "C45783", "MCU"),
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    "C91": ("Device:C", "100n", C0402, "C307331", "I2C"),
    "J4": ("Connector_Generic:Conn_01x04", "Qwiic 2", JST_SH4, "C160404", "I2C"),
    "J11": ("Connector_Generic:Conn_01x04", "I2C 2.54 (GND 3V3_SW SDA SCL)", "Connector_PinHeader_2.54mm:PinHeader_1x04_P2.54mm_Vertical", None, "I2C"),
    # Rain/wind/vane port J12 (JST PH 4-pin, hand-soldered): reed contacts to GND on RAIN_IN/WIND_IN, wind-vane resistor
    # network to GND on VANE_IN. Pins: IO15/IO16 = RTC GPIO (ULP counts in deep sleep), IO8 = ADC1_CH7 (usable with WiFi);
    # not strapping (0, 3, 45, 46), not USB (19, 20), not used elsewhere. Pull-ups 1M to +3V3: 3.3 uA per closed contact;
    # 1k + 4.7 nF at the pin: release edge 6.5 ms to VIH, 77 Hz max (calc/i2c_bus.py pulse rows).
    "J12": ("Connector_Generic:Conn_01x04", "RAIN/WIND (1 GND 2 RAIN 3 WIND 4 VANE)", "Connector_JST:JST_PH_B4B-PH-K_1x04_P2.00mm_Vertical", None, "Sensors"),
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    "CC2": [("J1", "B5"), ("R10", "1")],
    "USB_DP": [("J1", "A6"), ("J1", "B6"), ("U4", "1"), ("U4", "6"), ("R32", "1")],
    "USB_DN": [("J1", "A7"), ("J1", "B7"), ("U4", "3"), ("U4", "4"), ("R33", "1")],
    # SYS from the power board (or a bench supply on J10 pins 1/2): buck-boost, boost and test point
    "SYS": [("U2", "10"), ("U2", "1"), ("C40", "1"), ("U7", "3"), ("L5", "1"), ("C44", "1"), ("TP2", "1"), ("#FLG21", "1")],
    # Charger host pins: two I2C buses (charger on IO1/IO2, RTC I2C for the ULP core; sensors on IO13/IO14)
    "CHG_CE": [("R20", "2"), ("U1", "17")],
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    "RAIN_IN": [("J12", "2"), ("U10", "1"), ("U10", "6"), ("R70", "1"), ("R72", "1")],
    "WIND_IN": [("J12", "3"), ("U10", "3"), ("U10", "4"), ("R71", "1"), ("R73", "1")],
    "VANE_IN": [("J12", "4"), ("U11", "1"), ("U11", "6"), ("R74", "1"), ("R75", "1")],
    "RAIN": [("R72", "2"), ("C70", "1"), ("U1", "8")],    # IO15 (RTC GPIO)
    "WIND": [("R73", "2"), ("C71", "1"), ("U1", "9")],    # IO16 (RTC GPIO)
    "VANE": [("R75", "2"), ("C72", "1"), ("U1", "12")],   # IO8 = ADC1_CH7
    # Rails
    "3V3_SW": [("Q40", "3"), ("C42", "1"), ("C43", "1"), ("U8", "7"), ("U8", "19"), ("C47", "1"), ("R77", "1"), ("U5", "5"),
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TP_NOTE = "SYS/3V3 test pads"
# D+/D- join three sheets (USB, MCU, Header), the sensor bus three (MCU, Sensors, Ports): no crossing-free route on the
# root, so these keep labels there
ROOT_LABELLED = ("USB_DP", "USB_DN", "SEN_SDA", "SEN_SCL")
ROOT_TEXTS = [
    (6, 6, "#weatherstation main board: block diagram"),
    (6, 10, "Each box is a sheet. Wires join the sheet pins (hierarchical labels). Rails (GND, +3V3, 3V3_SW, SYS, USB_VBUS, 5V_SW) are power symbols."),
    (6, 68, "#Power flow (rails have no wires on this page)"),
    (6, 72, "power board --SYS (J10 on the USB sheet)--> Rails"),
    (6, 74, "Rails --+3V3 (TPS63802)--> MCU, USB (charger pull-ups), Sensors (pulse pull-ups)"),
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
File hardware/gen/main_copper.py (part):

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
  usb()        USB 2.0 pair J1 -> U4 (USBLC6 flow-through) -> R33/R32 (22 ohm) -> U1 pins 13/14, one F.Cu pair 0.27/0.15
               (90 ohm, calc/impedance.py), BC1.2 stubs on B.Cu to J10 pins 7/8, CC resistors, U4 VBUS/GND, GND stitching
  vbus()       USB_VBUS trunk J1 -> J10 pins 19/20 (1.6 A charge input)
  sys()        SYS trunk J10 pins 1/2 -> TPS63802 input cap and TPS61023 input
  buckboost()  TPS63802 U2 power stage (SLVSEU9D 12.1/12.2, figure 12-1)
  boost()      TPS61023 U7 power stage (SLVSF14B 10.1/10.2, figure 10-1)
  mcu()        ESP32 module decoupling at pin 2 with a GND via per cap
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

def anemometer(c):
    """J12 -> ESD in cable order, planar: VANE (pin 4) straight into U11, WIND (pin 3) and RAIN (pin 2) one level higher
    each into U10; each ESD channel's two pins joined under the body, GND pins by their own via between the lines."""
    P = c.P
    j2, j3, j4 = P("J12", "2"), P("J12", "3"), P("J12", "4")
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

def cluster(c, info):
    """Wind/rain/vane filter block and the three MCU lines to the module's left pins (locked, the autorouter left
    them open). Block: RAIN column (C70 / R72 / R70) and WIND column (C71 / R73 / R71) above U10, VANE column
    (C72 / R75 / R74) right of it. MCU lines: B.Cu bundle (0.5 mm pitch) west of J10, north through the window in
    the pair's B.Cu keepout (two GND planes between), RAIN and WIND on B.Cu into the pocket to vias at pins 8/9,
    VANE up to F.Cu right after the window and along the pair's north side (2 mm from its centre) to pin 12."""
    P = c.P
    W = 0.2
    a = {n: P("U10", str(n)) for n in range(1, 7)}
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    wm, vm = offset(jog, pb), offset(jog, -pb)
    yr, yw2 = 9.9, 9.4                                    # pocket runs: RAIN south, WIND north (RAIN turns first)
    u8, u9, u12 = P("U1", "8"), P("U1", "9"), P("U1", "12")
    pr = (u8[0] - 2.05, u8[1])                            # RAIN via, then F.Cu to pin 8 over WIND's B.Cu
    pw = (u9[0] - 1.3, u9[1])
    assert pw[0] - pr[0] > 0.7
    c.t("/MCU/RAIN", "B", wb, [vr] + jog + [(xr1, yr + 0.4), (xr1 + 0.4, yr), (pr[0] - (pr[1] - yr), yr), pr])
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    for p, u, net in ((pr, u8, "/MCU/RAIN"), (pw, u9, "/MCU/WIND")):
        c.v(net, *p)
        c.t(net, "F", W, [p, u])
    # VANE on F.Cu: parallel to the pair's diagonal, 2.0 mm from its centre on the north side, then into pin 12
    o = offset(info["centre"][1:3], 2.0)
    assert abs((o[1][0] - o[0][0]) - (o[1][1] - o[0][1])) < 1e-6, "45-degree descent"
    yf, ye = 10.1, u12[1] - 0.56
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

def boost_en(c):
    """BOOST_EN (module pin 20) to the via beside U7: the stubs (B.Cu) and the pair (F.Cu) close off U7's side, so the
    net drops into the pad band (via like the sensor I2C), runs west on B.Cu under the module, comes up north of the
    stubs and leaves on F.Cu through the corner gap between pins 14 and 15 (pin 15 is unused), then B.Cu again west
    of the stubs. Pins 17-19 keep their own escapes straight down and in the band."""
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

def gas_dac(c):
    """GAS_DAC (module pin 7, left column) cannot go south on the west side: the pair (F.Cu) and the stubs (B.Cu)
    interleave there. It drops to B.Cu next to the pin, runs under the module north of the BOOST_EN row, leaves the
    pad band between the BOOST_EN via and the SEN_SDA via, jogs west under the bottom pad row and runs south 1.7 mm
    east of the DN stub (outside emi.yaml's 1.0 mm parallel-run gap to USB copper), between the U2/C40 GND vias and
    RXD0, so B.Cu under the IO0 corner (R31; the LEDs sat there until 2026-11-24) stays free for the router's crossings; then F.Cu between
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    assert sda[1] < scl[1] < io0[1] and abs(j11[0] - j12[0]) < 1e-3 and j11[1] < j12[1] and j1[0] > j11[0]
    xb = sda[0] - 1.4                                    # via column in the band
    va, vb = (xb, sda[1]), (xb, scl[1])
    for net, pin, v in (("/MCU/CHG_SDA", sda, va), ("/MCU/CHG_SCL", scl, vb)):
        c.t(net, "F", W2, [pin, v])
        c.v(net, *v)
    xe_d, xe_c = sda[0] + 0.15, sda[0] - 0.35            # SDA outer (east), SCL inner, under the pad column
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
def pm_pocket(c):
    """PM sensor series resistors beside the module's left column: R48 (PM_TXD -> PM_RXIN) stands vertical, R49
    (PM_SET -> PM_SETIN) horizontal below it. PM_SET runs as one F.Cu diagonal from pin 6 between R48.2 and pin 7
    into R49.1, which leaves R48.2's west side free for PM_RXIN."""
    P = c.P
    p6, p7, r49, r48 = P("U1", "6"), P("U1", "7"), P("R49", "1"), P("R48", "2")
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

def gas_pair(c):
    """Pocket-to-window bundle: the gas module UART lines (U1 pin 11, R46.2) and PM_SETIN (R49.2), vias beside the
    pads, B.Cu north-west parallel to the pair's diagonal (outside its stitch vias), west, and south through the
    window in three lanes; the router takes all three on from just south of the pair (to J8/R47 and J2)."""
    P = c.P
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
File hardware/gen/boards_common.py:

"""Shared by power_board.py and main_board.py: footprints, the board-to-board header J10 (J_PWR) and its pin map.

The pin map lives here once, so both boards always agree (hardware/ARCHITECTURE.md has the table and the reasons;
hardware/tools/split_check.py proves both generators use it). Header net names are the netlist names: the contract
signal "VBUS" is the net USB_VBUS (USB-C VBUS before the charger's ACFET1/RBFET1 pair), "D+/D-" are USB_DP/USB_DN.
"""

R0603, C0603, C0805 = "Resistor_SMD:R_0603_1608Metric", "Capacitor_SMD:C_0603_1608Metric", "Capacitor_SMD:C_0805_2012Metric"
C0402, R0402 = "Capacitor_SMD:C_0402_1005Metric", "Resistor_SMD:R_0402_1005Metric"
JST_PH2 = "Connector_JST:JST_PH_B2B-PH-K_1x02_P2.00mm_Vertical"
JST_SH4 = "Connector_JST:JST_SH_SM04B-SRSS-TB_1x04-1MP_P1.00mm_Horizontal"
TP = "TestPoint:TestPoint_Pad_D1.5mm"
SOT23 = "Package_TO_SOT_SMD:SOT-23"

# J10 = J_PWR: keyed 2 x 10, 2.54 mm, through-hole, hand-soldered (no JLC fee). Odd pins = row A, even pins = row B.
# Pin HEADER_KEY is pulled from the main board's male header and its hole is blocked in the power board's socket; it has
# no net. Order (engineer 2026-11-21, hardware/tools/header_check.py): SYS on column 1, USB_VBUS on column 10, the key in
# column 2 and every signal in columns 4-8 with a GND pair between signal pairs. Then a 180 degree rotation, a mirror
# about either axis or a one-column offset puts a pin onto the blocked hole (cannot mate), and the remaining one-row
# offsets of an unshrouded header put SYS/USB_VBUS only onto GND or each other, never onto a signal pin.
HEADER_REF = "J10"
HEADER_COLS = 10
HEADER_KEY = 3
HEADER_SYMBOL = "Connector_Generic:Conn_02x10_Odd_Even"
HEADER_FOOTPRINT = "Connector_PinHeader_2.54mm:PinHeader_2x10_P2.54mm_Vertical"
HEADER_PINS = {
    "1": "SYS", "2": "SYS",
    "4": "GND",                      # pin 3 = key (removed, hole blocked)
    "5": "GND", "6": "GND",
    "7": "USB_DP", "8": "USB_DN",
    "9": "GND", "10": "GND",
    "11": "CHG_SDA", "12": "CHG_SCL",
    "13": "GND", "14": "GND",
    "15": "CHG_INT", "16": "CHG_CE",
    "17": "GND", "18": "GND",
    "19": "USB_VBUS", "20": "USB_VBUS",
}
HEADER_NETS = sorted(set(HEADER_PINS.values()))


def header_part(sheet: str, side: str) -> tuple:
    """PARTS entry of J10 on one board (side = 'power' or 'main'); same footprint on both so the holes line up."""
    kind = "male pins, pin 3 pulled" if side == "main" else "socket, hole 3 blocked"
    return (HEADER_SYMBOL, f"J_PWR 2x10 keyed 2.54 mm ({side} side: {kind}; hand-solder)", HEADER_FOOTPRINT, None, sheet)


def add_header(nets: dict) -> dict:
    """Append the J10 pins to the board's NETS (every header net must already exist on the board)."""
    for pin, net in HEADER_PINS.items():
        assert net in nets, f"header net {net} has no other pin on this board"
        nets[net].append((HEADER_REF, pin))
    return nets


# The pin table as a sheet note (beside J10 on both boards), one line per entry: KiCad's font is proportional, so no columns.
HEADER_NOTE = (
    "J10 pin map (hardware/ARCHITECTURE.md), keyed 2x10: pin 3 is the key (no pin, hole blocked)\n"
    "pins 1, 2: SYS, power board -> main board: system rail (cell-referred, 1.8-5.5 V), at least 1 A\n"
    "pins 4, 5, 6, 9, 10, 13, 14, 17, 18: GND (a GND pair between every signal pair)\n"
    "pins 7, 8: USB_DP, USB_DN, main -> power: BC1.2 detection only (BQ25798 D+/D-)\n"
    "pins 11, 12: CHG_SDA, CHG_SCL: charger I2C (address 0x6B), 10k pull-ups on the main board\n"
    "pin 15: CHG_INT, power -> main: open drain, 10k pull-up on the main board\n"
    "pin 16: CHG_CE, main -> power: active low, pulled high (charge off) until firmware drives it low\n"
    "pins 19, 20: USB_VBUS, main -> power: USB-C VBUS to ACFET1 drain and VAC1\n"
    "Rotated, mirrored or column-shifted plugs hit the key (tools/header_check.py). No 3.3 V on the power board.")

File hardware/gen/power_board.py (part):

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    "C2": ("Device:C", "0.1u", C0402, "C307331", "Inputs"),
    # 6 V class PV panel (Voc about 8 V cold): SMBJ10A standoff 10 V, clamp 17 V, below the 30 V abs max of VAC2/AO3400A
    # (v1 PARTS-REVIEW A6, decided 2026-11-01). Littelfuse part.
    # unidirectional TVS (review A6): Zener-shape symbol, pin 1 = K on PV_RAW, pin 2 = A on PV_N_RAW
    "D1": ("Device:D_Zener", "SMBJ10A (PV surge, standoff 10 V, clamp 17 V)", "Diode_SMD:D_SMB", "C151250", "Inputs"),
    # 2-line common-mode choke on the PV pair: winding A = 1 -> 2, winding B = 4 -> 3 (EMTEK T-0602-102D equivalent circuit;
    # LCSC maker HongyeX). 3 A, 70 mohm DCR, 90 ohm at 100 MHz. Footprint weatherstation:CMF4532F_4P (fixed 2026-11-05).
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    "TS": [("U3", "16"), ("R17", "2"), ("R18", "1"), ("TH1", "1")],
    "STAT": [("U3", "1"), ("D2", "1")],
    "LED_A": [("R19", "2"), ("D2", "2")],
    # QON (pin 12) left open: internal pull-up (v1 PARTS-REVIEW C, R21 removed 2026-11-01); no-connect marker.
    # Host pins: pull-ups R20 (CE), R22 (INT), R54/R55 (I2C) to +3V3 are on the main board (no 3.3 V here).
    "CHG_CE": [("U3", "13"), ("R23", "1")],
    "QON": [("U3", "12"), ("TP3", "1")],
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HAND_SOLDER = {"J5", "J6", "J10"}  # JST PH and the 2.54 mm header: hand-soldered, not in the assembly BOM
ROOT_TEXTS = [
    (6, 6, "#weatherstation power board: block diagram"),
    (6, 10, "Each box is a sheet. Wires join the sheet pins (hierarchical labels). Rails (GND, SYS, VBUS, USB_VBUS, PMID, REGN, BAT_PACK) are power symbols."),
    (6, 66, "#Power flow (rails have no wires on this page)"),
    (6, 70, "main board USB-C --USB_VBUS (J10)--> Inputs: ACFET1/RBFET1 --VBUS--> Charger"),
    (6, 72, "solar panel J5 --PV_IN (TVS, choke)--> Inputs: ACFET2/RBFET2 --VBUS--> Charger"),
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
